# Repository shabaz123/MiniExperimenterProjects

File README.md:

# MiniExperimenterProjects
 
## Go To The Projects

Click to select a project!

[Remote Control Detector](https://github.com/shabaz123/MiniExperimenterProjects/tree/main/RemoteControlDetector): A simple project that can detect when a button is pressed on an infra-red remote control! Most TV remotes will work (you can check by pointing the remote at your mobile phone camera, pressing any button, and seeing if you can see a faint glow when viewing the video from the camera).

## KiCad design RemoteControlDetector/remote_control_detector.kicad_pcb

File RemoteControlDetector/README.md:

# Remote Control Detector

This project can be used to detect infra-red remote controls!

## What Does it Do?

Press a button on any remote control (well, infra-red based remote controls) such as a TV remote, and the light-emitting diode (LED) will flash!

## How Does it Work?

All TVs contain a little integrated circuit (IC) that senses light with an internal photodiode, and then amplifies the signal provided it is changing rapidly (at about 38 kHz). An output signal indicates the presence of the rapidly changing light. The circuit uses such an integrated circuit, part code TL1838. 

Beyond that, all that is needed in the circuit is a way to reduce or regulate the power to the chip (it needs to be less than 5V not to damage it). An LED is connected to the output of the chip, through a resistor to limit the current (LEDs don’t need a lot of power).

## Downloads

[PDF circuit diagram and pinouts](remote_control_detector_schematic.pdf)

## Circuit Diagram

## Pinouts

## Components List

    COMPONENTS LIST
    R1, R2: 10k RESISTORS
    R3: 220 ohm RESISTOR
    Q1: BC547 NPN TRANSISTOR
    C1: 10uF CAPACITOR
    U1: TL1831 INFRA-RED 38kHz SENSOR
    D1: LIGHT EMITTING DIODE (LED)

## Photos and Video

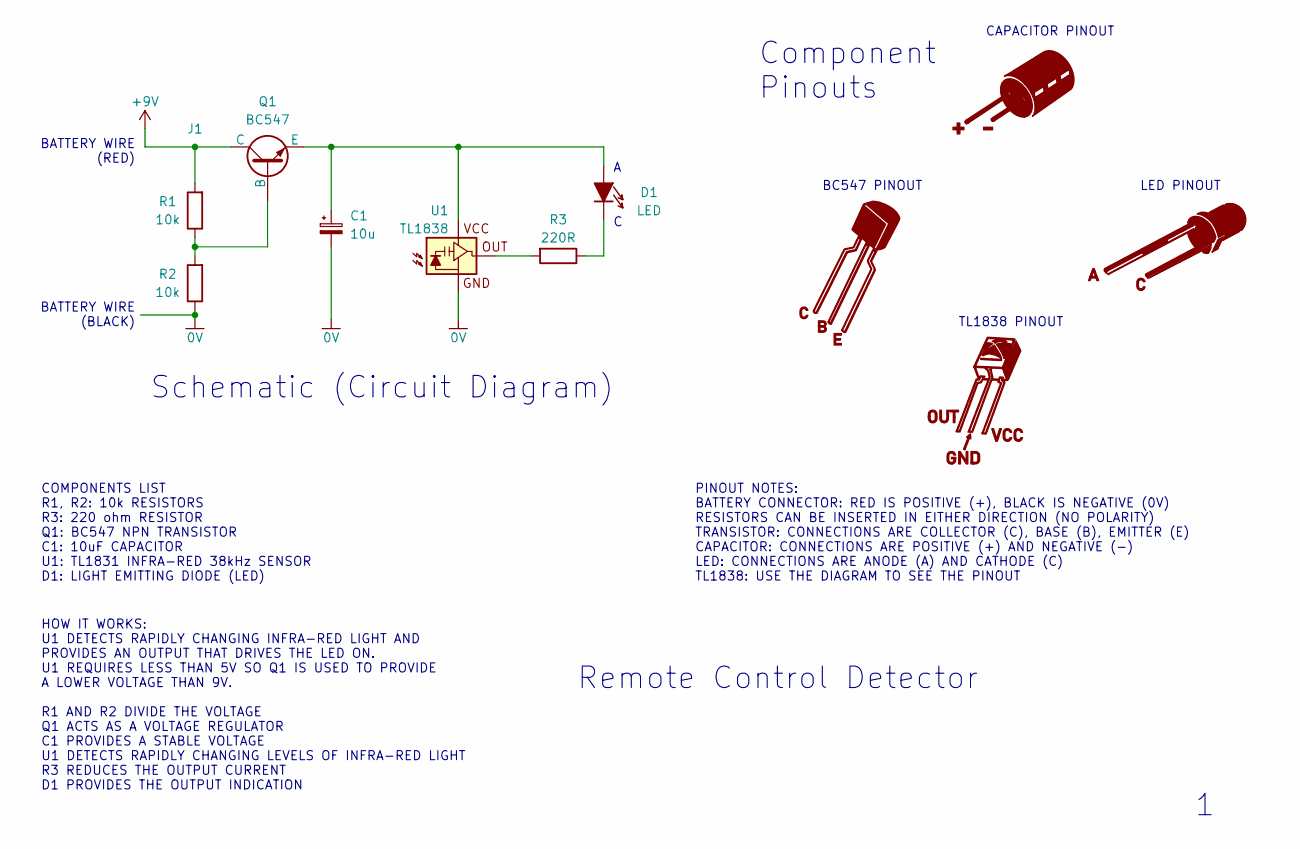
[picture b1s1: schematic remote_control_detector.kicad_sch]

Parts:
C1: 10u; CP_Radial_D5.0mm_P2.50mm
D1: LED; LED_3mm
J1, J2: Terminal-Single-Hole-1mm
Q1: BC547; TO-92_Wide_BJT
R1, R2: 10k; R_Axial_DIN0207_L6.3mm_D2.5mm_P10.16mm_Horizontal
R3: 220R; R_Axial_DIN0207_L6.3mm_D2.5mm_P10.16mm_Horizontal
U1: TL1838

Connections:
0V: C1.2, J2.1, R2.1, U1.2
+9V: J1.1, Q1.1 (C), R1.2
unnamed: C1.1, D1.2 (A), Q1.3 (E), U1.3
unnamed: D1.1 (K), R3.1
unnamed: Q1.2 (B), R1.1, R2.2
unnamed: R3.2, U1.1

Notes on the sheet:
TL1838 PINOUT
BC547 PINOUT
Component Pinouts
Schematic (Circuit Diagram)
Remote Control Detector
COMPONENTS LIST R1, R2: 10k RESISTORS R3: 220 ohm RESISTOR Q1: BC547 NPN TRANSISTOR C1: 10uF CAPACITOR U1: TL1831 INFRA-RED 38kHz SENSOR D1: LIGHT EMITTING DIODE (LED)
BATTERY WIRE (BLACK)
HOW IT WORKS: U1 DETECTS RAPIDLY CHANGING INFRA-RED LIGHT AND PROVIDES AN OUTPUT THAT DRIVES THE LED ON. U1 REQUIRES LESS THAN 5V SO Q1 IS USED TO PROVIDE A LOWER VOLTAGE THAN 9V. R1 AND R2 DIVIDE THE VOLTAGE Q1 ACTS AS A VOLTAGE REGULATOR C1 PROVIDES A STABLE VOLTAGE U1 DETECTS RAPIDLY CHANGING LE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
BATTERY WIRE (RED)
LED PINOUT
PINOUT NOTES: BATTERY CONNECTOR: RED IS POSITIVE (+), BLACK IS NEGATIVE (0V) RESISTORS CAN BE INSERTED IN EITHER DIRECTION (NO POLARITY) TRANSISTOR: CONNECTIONS ARE COLLECTOR (C), BASE (B), EMITTER (E) CAPACITOR: CONNECTIONS ARE POSITIVE (+) AND NEGATIVE (-) LED: CONNECTIONS ARE ANODE (A) AND CATHO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
CAPACITOR PINOUT

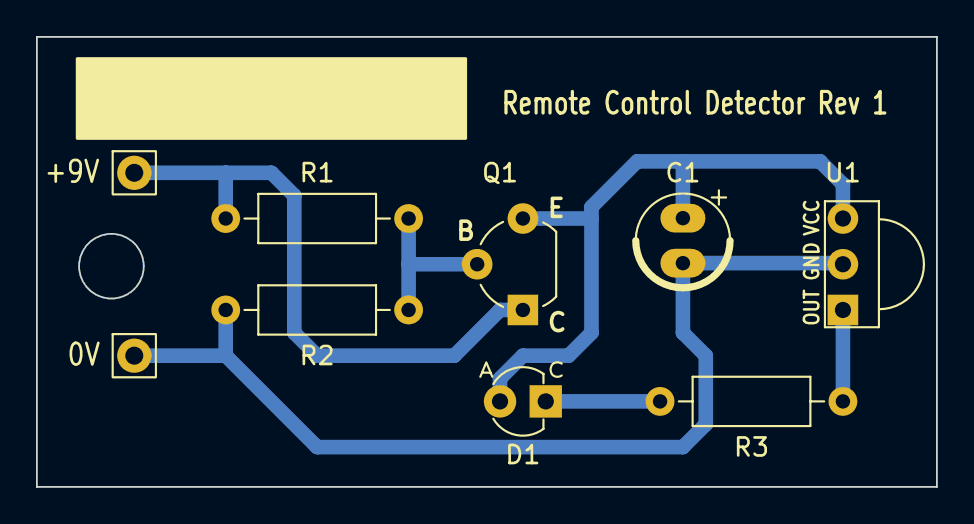
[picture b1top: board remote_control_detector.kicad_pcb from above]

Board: 2 copper layers, 50.0 x 25.0 mm, 9 parts (0 on the bottom side), 6 nets.

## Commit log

2023-09-02 Initial version
    Initial version
